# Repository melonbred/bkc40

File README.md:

# bkc40
 base kit compatible 40

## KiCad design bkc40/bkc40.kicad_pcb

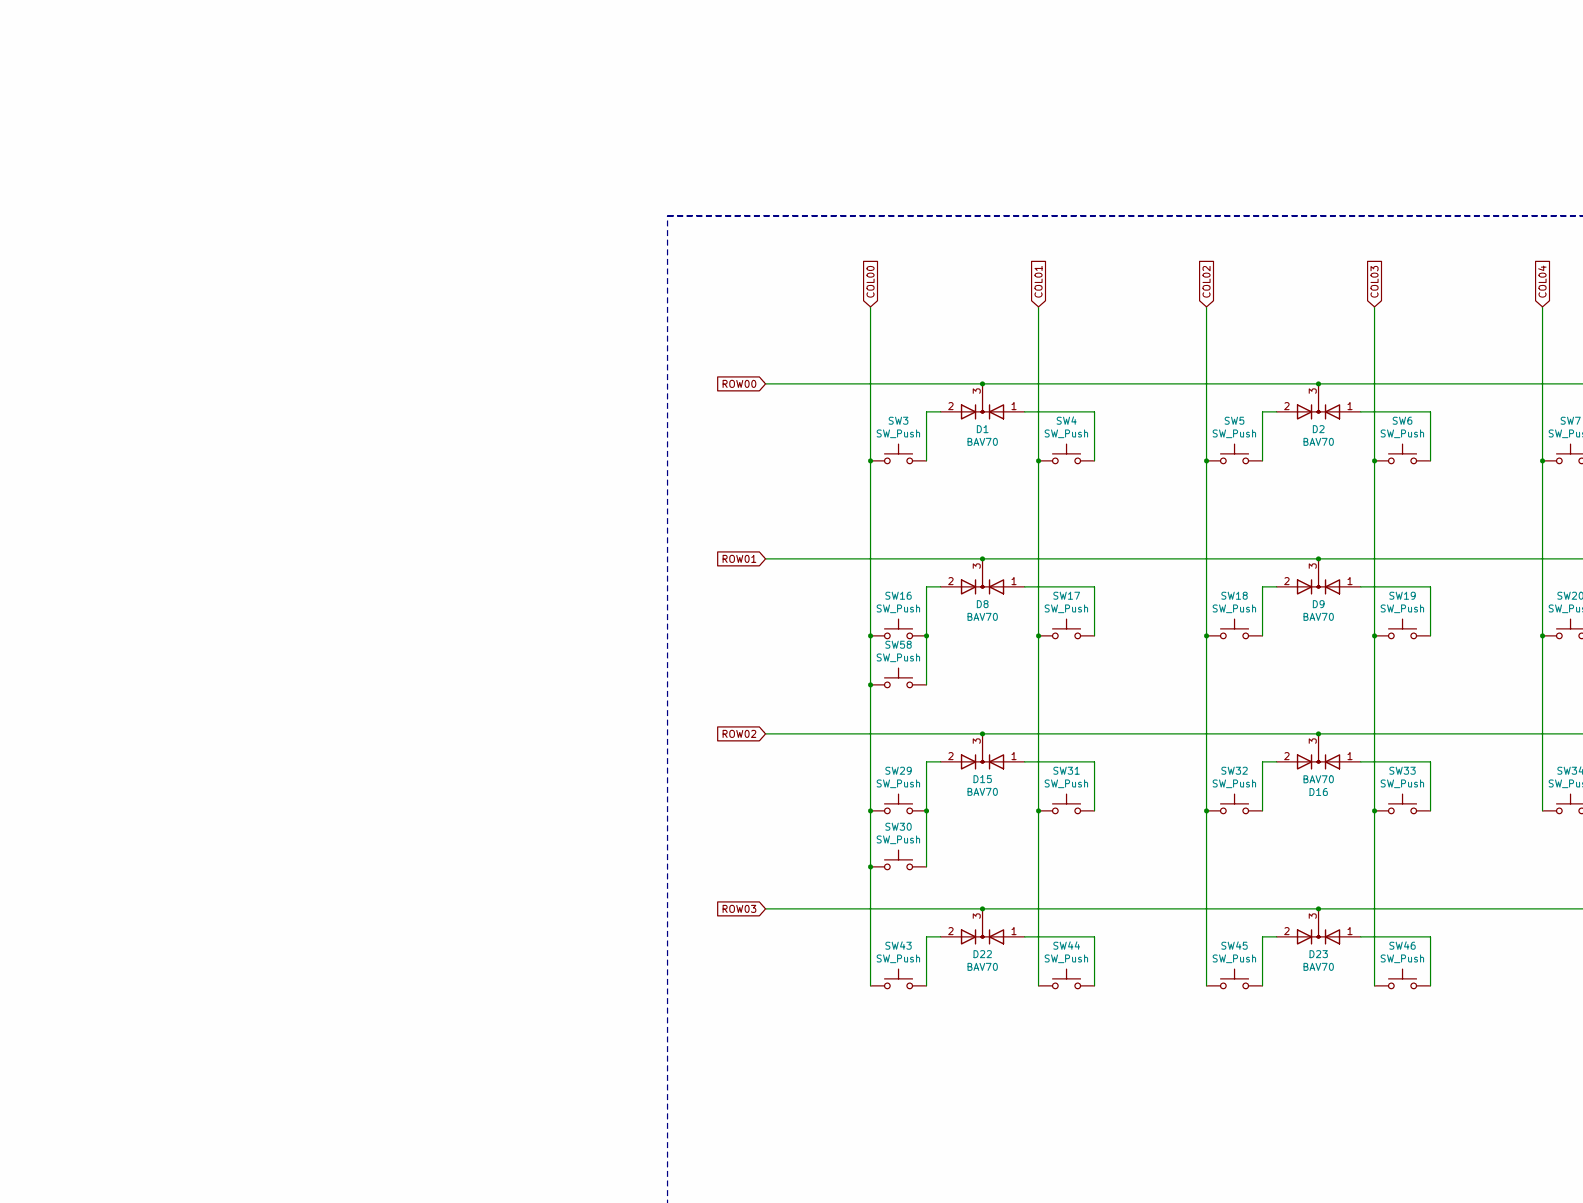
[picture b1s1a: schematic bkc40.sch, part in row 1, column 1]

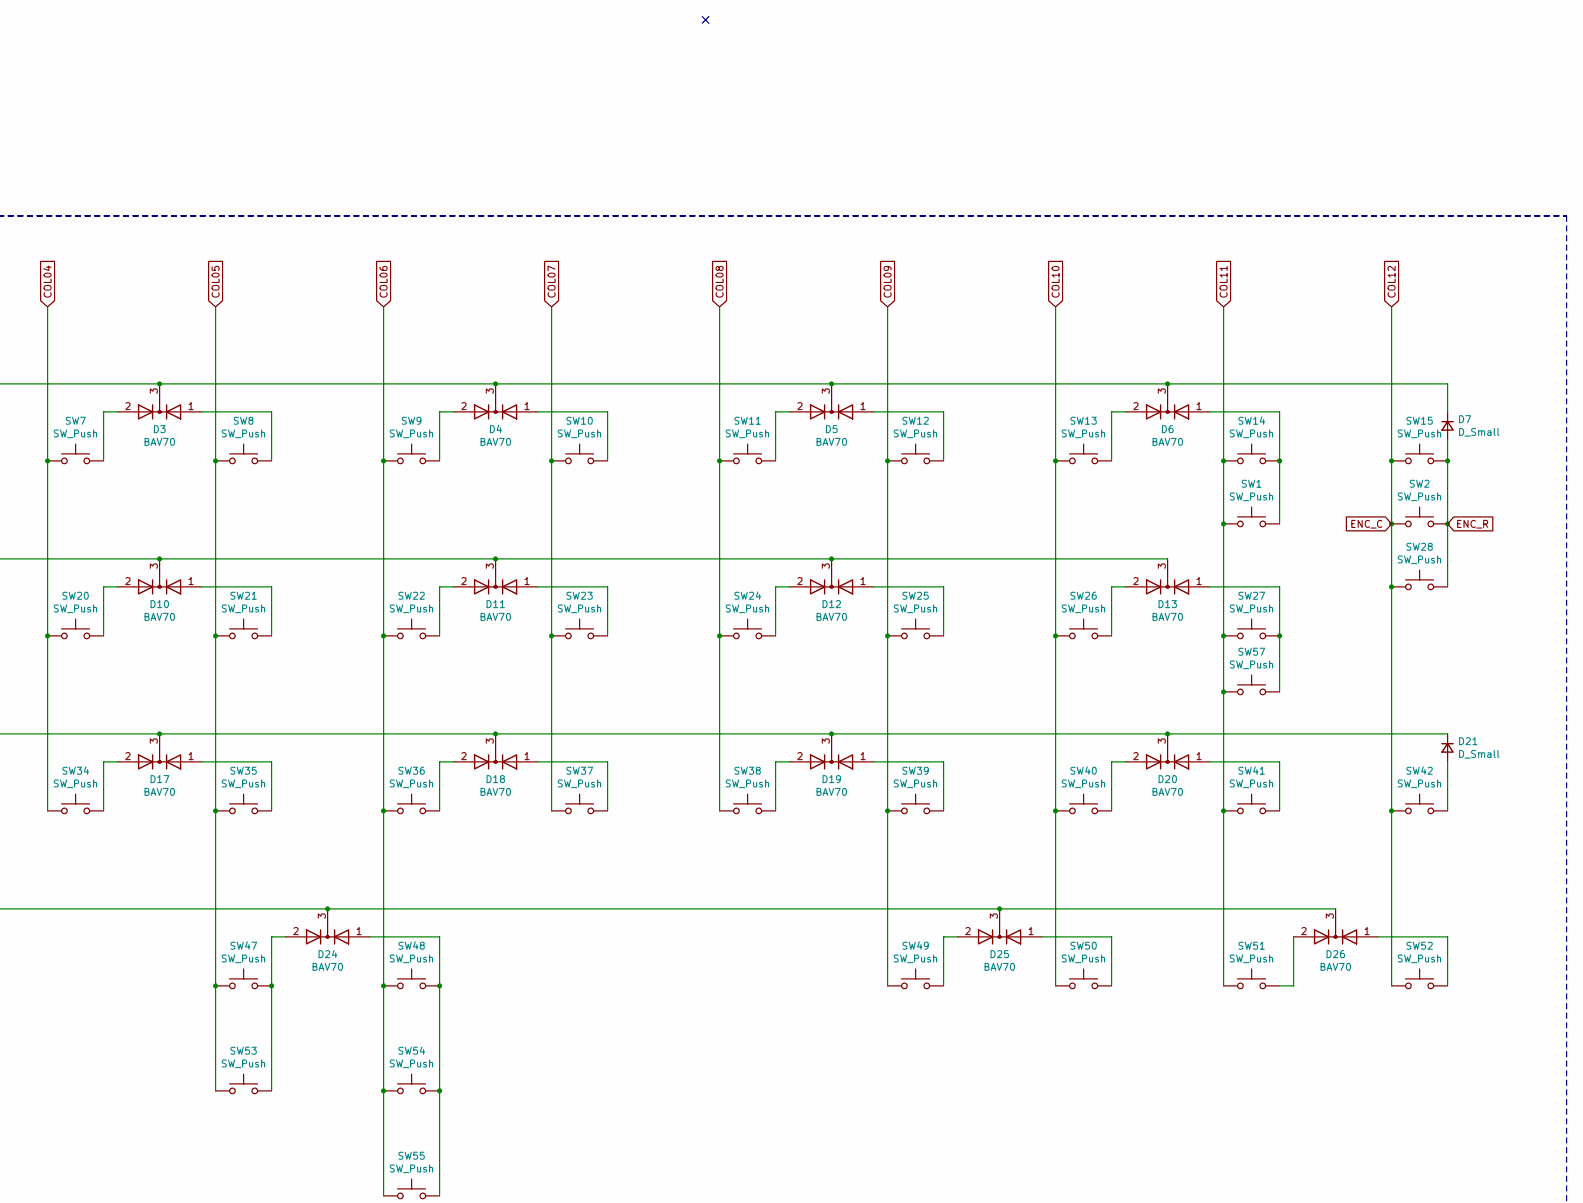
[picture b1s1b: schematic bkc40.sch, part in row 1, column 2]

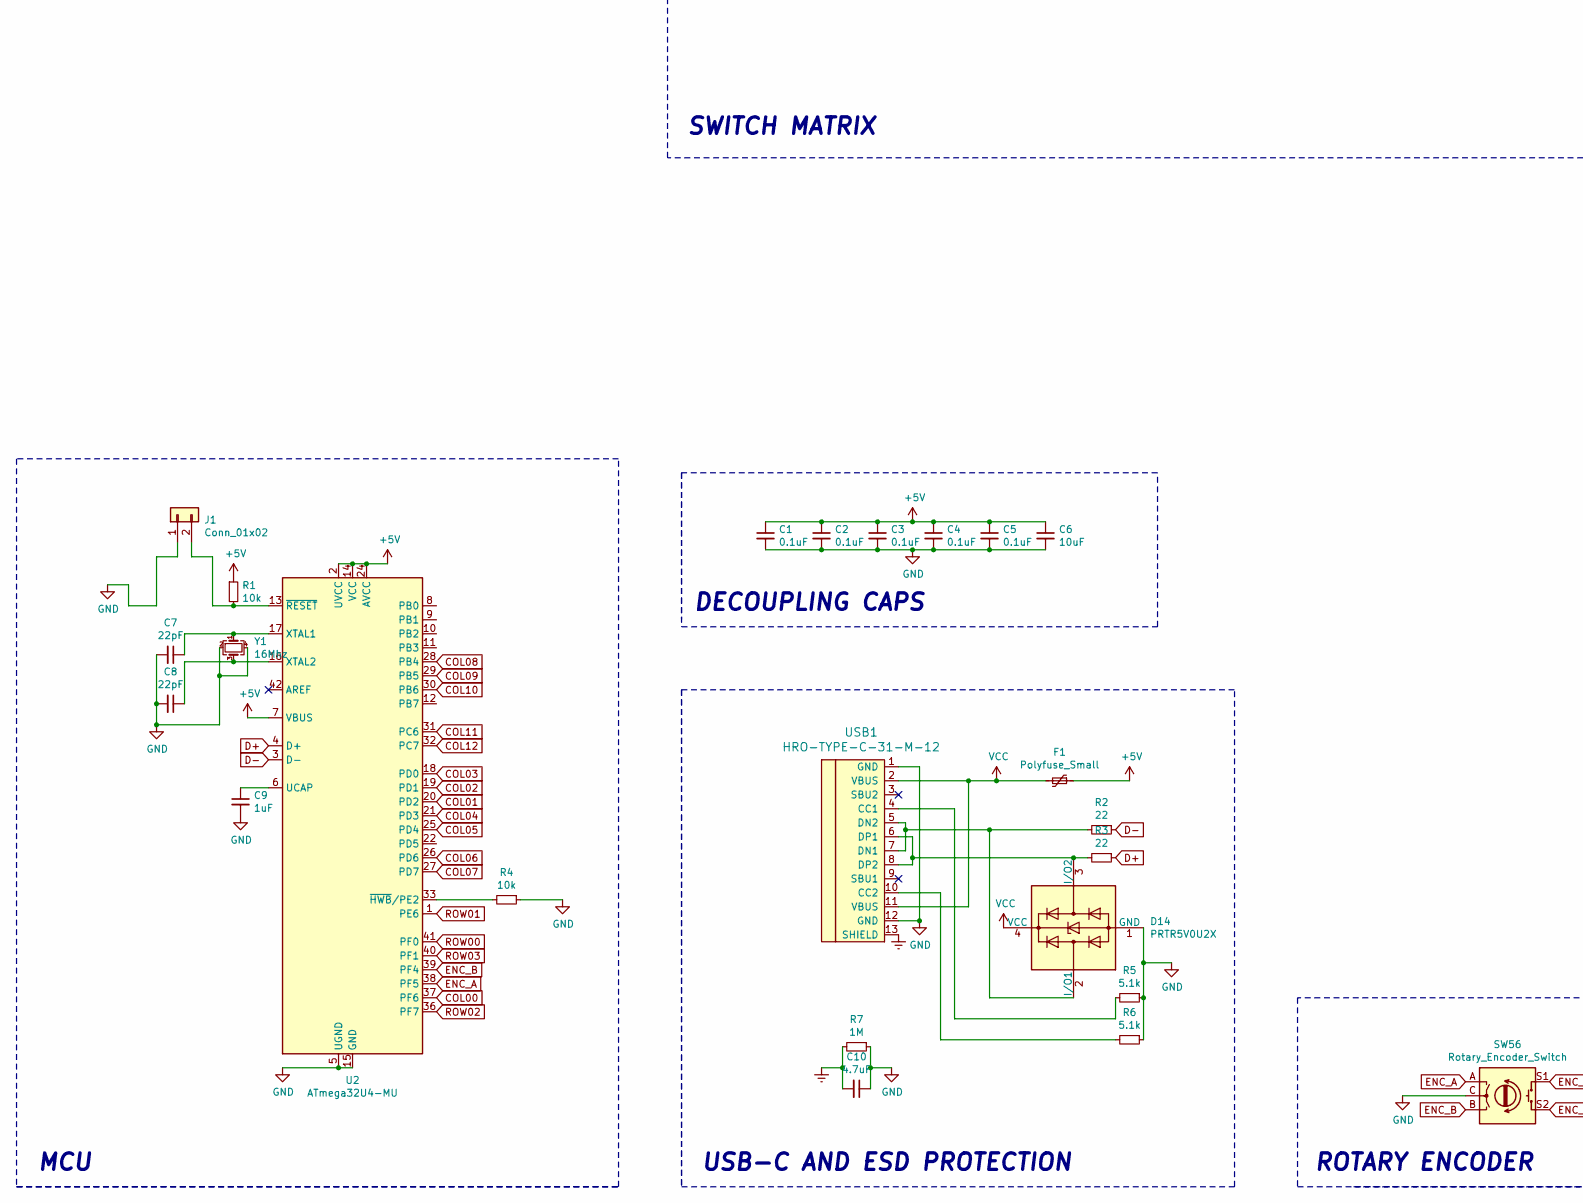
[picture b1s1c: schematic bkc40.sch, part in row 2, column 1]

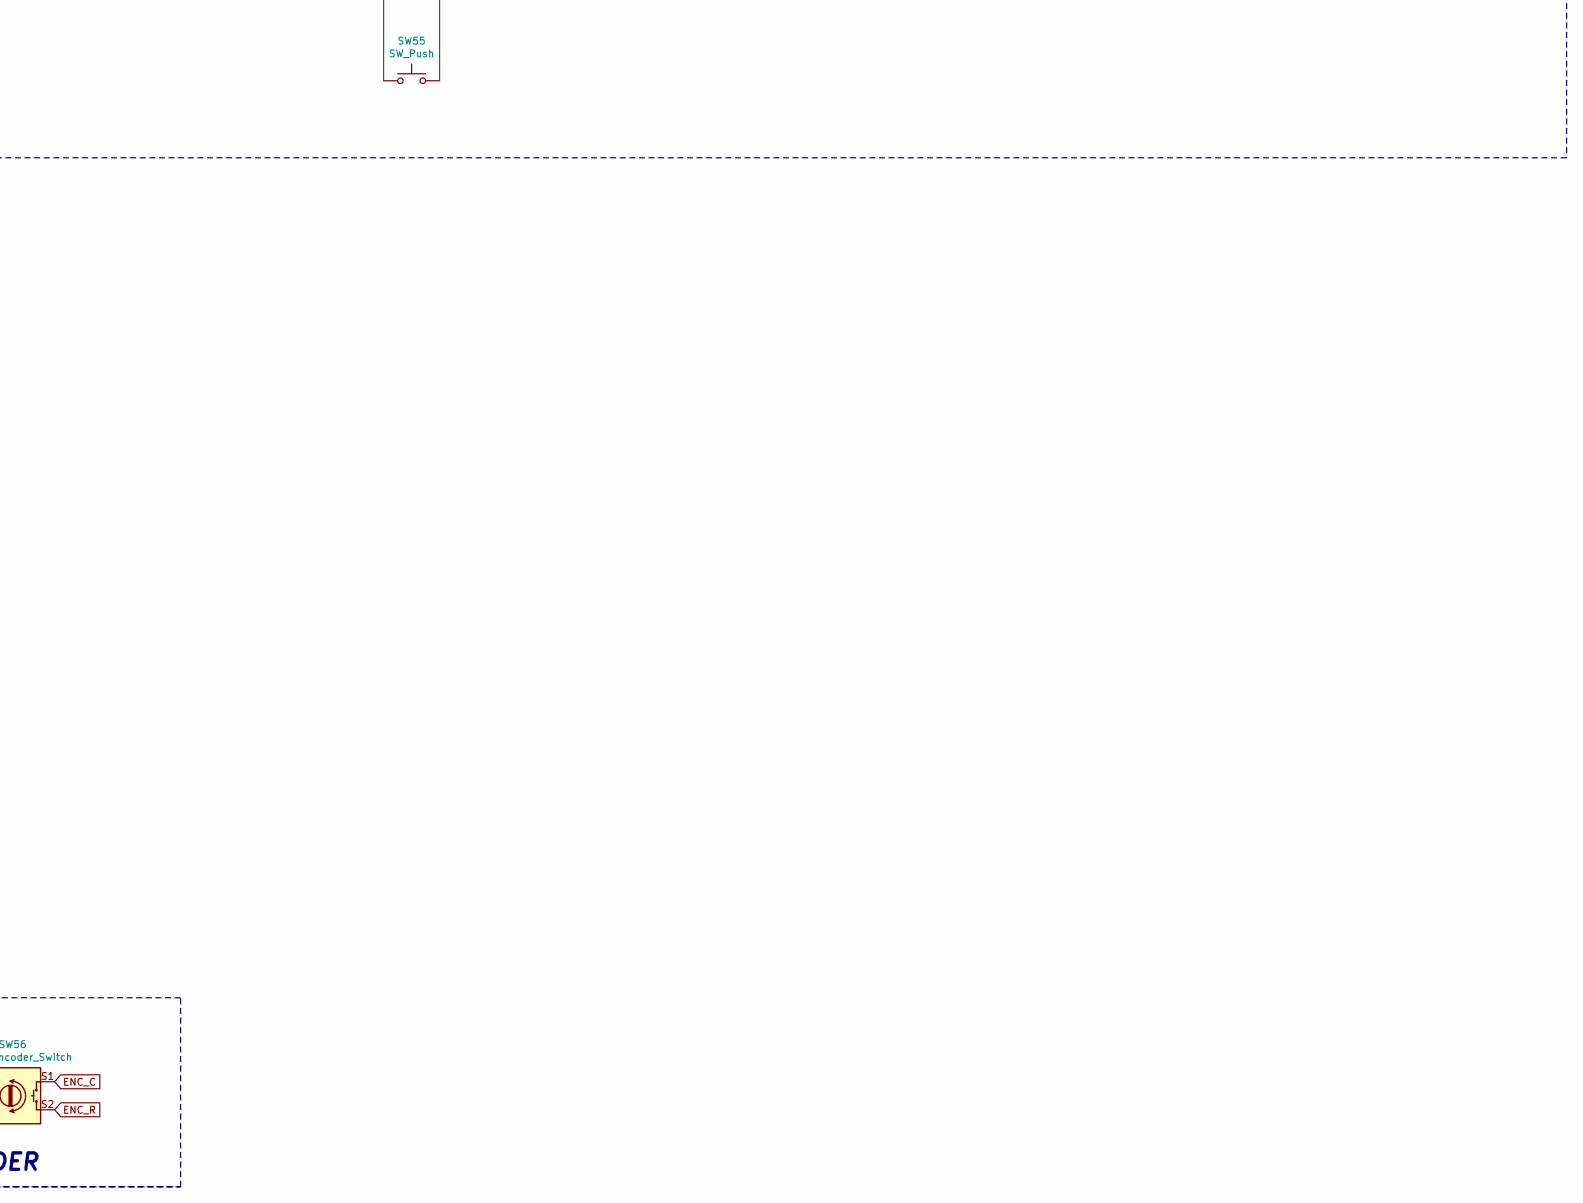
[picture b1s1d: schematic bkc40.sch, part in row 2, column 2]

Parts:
C1, C2, C3, C4, C5: 0.1uF; C_0603_1608Metric
C6: 10uF; C_0603_1608Metric
C7, C8: 22pF; C_0603_1608Metric
C9: 1uF; C_0603_1608Metric
C10: 4.7uF; C_0603_1608Metric
D1, D2, D3, D4, D5, D6, D8, D9, D10, D11, D12, D13, D15, D16, D17, D18, D19, D20, D22, D23, D24, D25, D26: BAV70; SOT-23
D7, D21: D_Small; D_SOD-123
D14: PRTR5V0U2X; SOT-143
F1: Polyfuse_Small; Fuse_1206_3216Metric
J1: Conn_01x02; PinHeader_1x02_P2.54mm_Vertical
R1, R4: 10k; R_0603_1608Metric
R2, R3: 22; R_0603_1608Metric
R5, R6: 5.1k; R_0603_1608Metric
R7: 1M; R_0603_1608Metric
SW1, SW3, SW15: SW_Push; MXOnly-1.5U-NoLED
SW2, SW4, SW5, SW6, SW7, SW8, SW9, SW10, SW11, SW12, SW13, SW14, SW17, SW18, SW19, SW20, SW21, SW22, SW23, SW24, SW25, SW26, SW27, SW31, SW32, SW33, SW34, SW35, SW36, SW37, SW38, SW39, SW40, SW41, SW44, SW46, SW49, SW51: SW_Push; MXOnly-1U-NoLED
SW16, SW42: SW_Push; MXOnly-1.75U-NoLED
SW28: SW_Push; MXOnly-ISO-ReversedStabilizers-NoLED
SW29: SW_Push; MXOnly-2.25U-NoLED
SW30, SW43, SW45, SW50, SW52, SW58: SW_Push; MXOnly-1.25U-NoLED
SW47, SW57: SW_Push; MXOnly-2.25U-ReversedStabilizers-NoLED
SW48: SW_Push; MXOnly-2.75U-ReversedStabilizers-NoLED
SW53, SW54: SW_Push; MXOnly-3U-ReversedStabilizers-NoLED
SW55: SW_Push; MXOnly-7U-ReversedStabilizers-NoLED
SW56: Rotary_Encoder_Switch; RotaryEncoder_Alps_EC11E-Switch_Vertical_H20mm
U2: ATmega32U4-MU; QFN-44-1EP_7x7mm_P0.5mm_EP5.2x5.2mm
USB1: HRO-TYPE-C-31-M-12; HRO-TYPE-C-31-M-12-Assembly
Y1: 16Mhz; Crystal_SMD_3225-4Pin_3.2x2.5mm

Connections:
+5V: C1.1, C2.1, C3.1, C4.1, C5.1, C6.1, F1.1, R1.1, U2.2 (UVCC), U2.7 (VBUS), U2.14 (VCC), U2.24 (AVCC), U2.34 (VCC), U2.44 (AVCC)
COL00: SW3.1, SW16.1, SW29.1, SW30.1, SW43.1, SW58.1, U2.37 (PF6)
COL01: SW4.1, SW17.1, SW31.1, SW44.1, U2.20 (PD2)
COL02: SW5.1, SW18.1, SW32.1, SW45.1, U2.19 (PD1)
COL03: SW6.1, SW19.1, SW33.1, SW46.1, U2.18 (PD0)
COL04: SW7.1, SW20.1, SW34.1, U2.21 (PD3)
COL05: SW8.1, SW21.1, SW35.1, SW47.1, SW53.1, U2.25 (PD4)
COL06: SW9.1, SW22.1, SW36.1, SW48.1, SW54.1, SW55.1, U2.26 (PD6)
COL07: SW10.1, SW23.1, SW37.1, U2.27 (PD7)
COL08: SW11.1, SW24.1, SW38.1, U2.28 (PB4)
COL09: SW12.1, SW25.1, SW39.1, SW49.1, U2.29 (PB5)
COL10: SW13.1, SW26.1, SW40.1, SW50.1, U2.30 (PB6)
COL11: SW1.1, SW14.1, SW27.1, SW41.1, SW51.1, SW57.1, U2.31 (PC6)
COL12: SW2.1, SW15.1, SW28.1, SW42.1, SW52.1, SW56.S1, U2.32 (PC7)
D+: R3.1, U2.4 (D+)
D-: R2.1, U2.3 (D-)
ENC_A: SW56.A, U2.38 (PF5)
ENC_B: SW56.B, U2.39 (PF4)
ENC_R: D7.2 (A), SW2.2, SW15.2, SW28.2, SW56.S2
Earth: C10.2, R7.2, USB1.13 (SHIELD)
GND: C1.2, C2.2, C3.2, C4.2, C5.2, C6.2, C7.2, C8.2, C9.2, C10.1, D14.1 (GND), J1.1, R4.1, R5.1, R6.1, R7.1, SW56.C, U2.5 (UGND), U2.15 (GND), U2.23 (GND), U2.35 (GND), U2.43 (GND), U2.45 (GND), USB1.1 (GND), USB1.12 (GND), Y1.2, Y1.4
unnamed: C7.1, U2.17 (XTAL1), Y1.1
unnamed: C8.1, U2.16 (XTAL2), Y1.3
unnamed: C9.1, U2.6 (UCAP)
unnamed: D1.1 (A), SW4.2
unnamed: D1.2 (A), SW3.2
unnamed: D2.1 (A), SW6.2
unnamed: D2.2 (A), SW5.2
unnamed: D3.1 (A), SW8.2
unnamed: D3.2 (A), SW7.2
unnamed: D4.1 (A), SW10.2
unnamed: D4.2 (A), SW9.2
unnamed: D5.1 (A), SW12.2
unnamed: D5.2 (A), SW11.2
unnamed: D6.1 (A), SW1.2, SW14.2
unnamed: D6.2 (A), SW13.2
unnamed: D8.1 (A), SW17.2
unnamed: D8.2 (A), SW16.2, SW58.2
unnamed: D9.1 (A), SW19.2
unnamed: D9.2 (A), SW18.2
unnamed: D10.1 (A), SW21.2
unnamed: D10.2 (A), SW20.2
unnamed: D11.1 (A), SW23.2
unnamed: D11.2 (A), SW22.2
unnamed: D12.1 (A), SW25.2
unnamed: D12.2 (A), SW24.2
unnamed: D13.1 (A), SW27.2, SW57.2
unnamed: D13.2 (A), SW26.2
unnamed: D14.2 (I/O1), R2.2, USB1.5 (DN2), USB1.7 (DN1)
unnamed: D14.3 (I/O2), R3.2, USB1.6 (DP1), USB1.8 (DP2)
unnamed: D15.1 (A), SW31.2
unnamed: D15.2 (A), SW29.2, SW30.2
unnamed: D16.1 (A), SW33.2
unnamed: D16.2 (A), SW32.2
unnamed: D17.1 (A), SW35.2
unnamed: D17.2 (A), SW34.2
unnamed: D18.1 (A), SW37.2
unnamed: D18.2 (A), SW36.2
unnamed: D19.1 (A), SW39.2
unnamed: D19.2 (A), SW38.2
unnamed: D20.1 (A), SW41.2
unnamed: D20.2 (A), SW40.2
unnamed: D21.2 (A), SW42.2
unnamed: D22.1 (A), SW44.2
unnamed: D22.2 (A), SW43.2
unnamed: D23.1 (A), SW46.2
unnamed: D23.2 (A), SW45.2
unnamed: D24.1 (A), SW48.2, SW54.2, SW55.2
unnamed: D24.2 (A), SW47.2, SW53.2
unnamed: D25.1 (A), SW50.2
unnamed: D25.2 (A), SW49.2
unnamed: D26.1 (A), SW52.2
unnamed: D26.2 (A), SW51.2
unnamed: J1.2, R1.2, U2.13 (~RESET)
unnamed: R4.2, U2.33 (~HWB~/PE2)
unnamed: R5.2, USB1.4 (CC1)
unnamed: R6.2, USB1.10 (CC2)
ROW00: D1.3 (K), D2.3 (K), D3.3 (K), D4.3 (K), D5.3 (K), D6.3 (K), D7.1 (K), U2.41 (PF0)
ROW01: D8.3 (K), D9.3 (K), D10.3 (K), D11.3 (K), D12.3 (K), D13.3 (K), U2.1 (PE6)
ROW02: D15.3 (K), D16.3 (K), D17.3 (K), D18.3 (K), D19.3 (K), D20.3 (K), D21.1 (K), U2.36 (PF7)
ROW03: D22.3 (K), D23.3 (K), D24.3 (K), D25.3 (K), D26.3 (K), U2.40 (PF1)
VCC: D14.4 (VCC), F1.2, USB1.2 (VBUS), USB1.11 (VBUS)

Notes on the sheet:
MCU
USB-C AND ESD PROTECTION
DECOUPLING CAPS
SWITCH MATRIX
ROTARY ENCODER

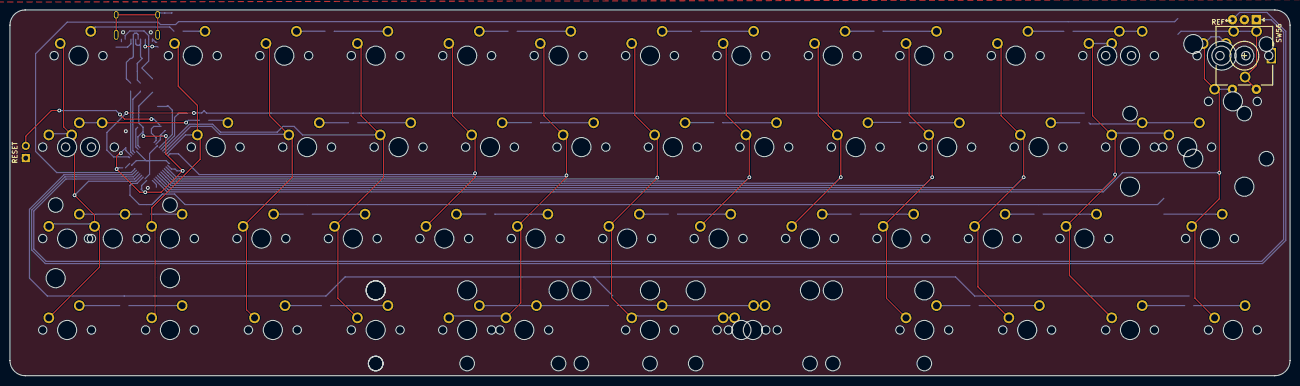
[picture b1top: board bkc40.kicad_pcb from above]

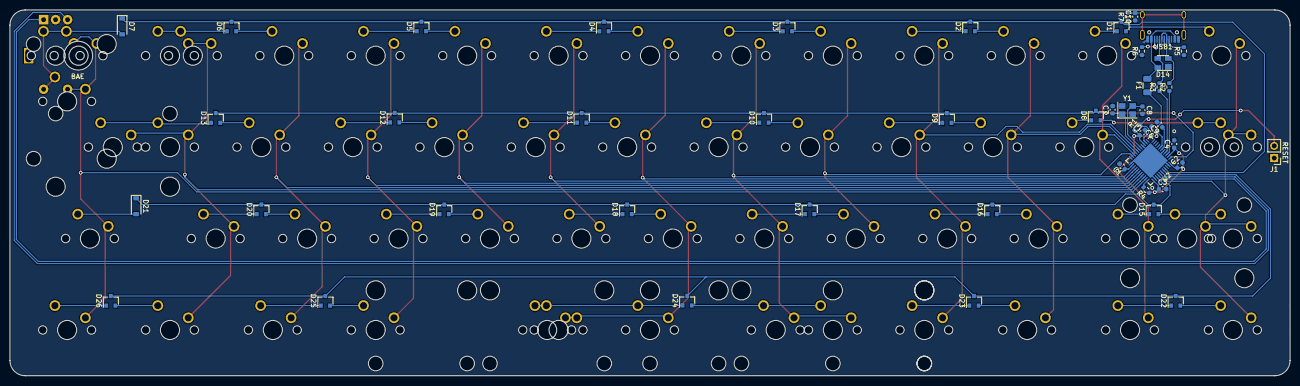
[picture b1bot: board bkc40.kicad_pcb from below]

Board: 2 copper layers, 266.7 x 76.2 mm, 106 parts (48 on the bottom side), 82 nets.

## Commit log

2021-08-27 Initialize project
2021-08-27 Add submodules
2021-08-27 Add submodule
2021-08-27 Add footprint libraries
2021-08-27 rev01
2021-08-27 step export
2021-09-25 update cc pins
2023-07-07 PCB update
